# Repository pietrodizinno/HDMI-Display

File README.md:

# HDMI-Display / HDMI to RGB Adapter
Universal HDMI/DVI Displays with Touch Panel based on TI TFP401 and Atmel ATmega32u4 (with Arduino Leonardo compatible Bootloader).

## Shop
* [HDMI to RGB Adapter](http://www.watterott.com/en/HDMI-RGB-adapter-with-ATmega32U4-touch-controller)
* [40-Pin FFC-Extenter](http://www.watterott.com/en/40-Pin-FFC-extenter)
* [Bundle: HDMI Adapter + 5" 800x480 Display with Touchpanel](http://www.watterott.com/en/5-800x480-HDMI-Display-with-resistive-touch)
* [Bundle: HDMI Adapter + 7" 800x480 Display with Touchpanel](http://www.watterott.com/en/7-800x480-HDMI-Display-with-resistive-touch)
* Compatible TFT-Displays *(check jumper settings before connecting the screen)*:
  * [5" 800x480 Display with resitive Touchpanel](http://www.watterott.com/en/5-800x480-TFT-Display)
  * [7" 800x480 Display with resitive Touchpanel](http://www.watterott.com/en/7-800x480-TFT-Display)
  * [7" 800x480 Display with capacitive Touchpanel](http://www.watterott.com/en/7-inch-800x480-TFT-LCD-Display-with-capacitive-touch-panel)
  * [7" 1024x600 Display with capacitive Touchpanel](http://www.watterott.com/en/7-inch-1024x600-TFT-LCD-Display-with-capacitive-touch-panel) *(needs hardware modification on backlight circuit)*

## Features
* TI **TFP401A** HDMI to RGB Converter
* Pixel Rates up to 165MHz, 1080p and WUXGA (1920x1200) at 60Hz
* HDMI compatible (DVI, no Sound, no HDCP, no CEC)
* Atmel **ATmega32U4** Microcontroller to control Backlight and Touch Panel (USB HID Mouse)
* **EDID** EEPROM (24LC02B) for display settings
* LED Backlight Boost Regulator (up to 35V)
* 3.3V - 5V tolerant UART and I2C interface
* **Single 5V Power Supply** via MicroUSB connector

## Hardware and Software
* [Schematics/Layout + Guide](https://github.com/watterott/HDMI-Display/tree/master/pcb)
* [Firmware for ATmega32U4 Microcontroller](https://github.com/watterott/HDMI-Display/tree/master/src)
* [Displays Compatibility List](https://github.com/watterott/HDMI-Display/blob/master/docu/Displays.md)
* [FAQ (Frequently Asked Questions)](https://github.com/watterott/HDMI-Display/blob/master/docu/FAQ.md)
* [Enclosures (3D models)](https://www.thingiverse.com/search?q=watterott+display)

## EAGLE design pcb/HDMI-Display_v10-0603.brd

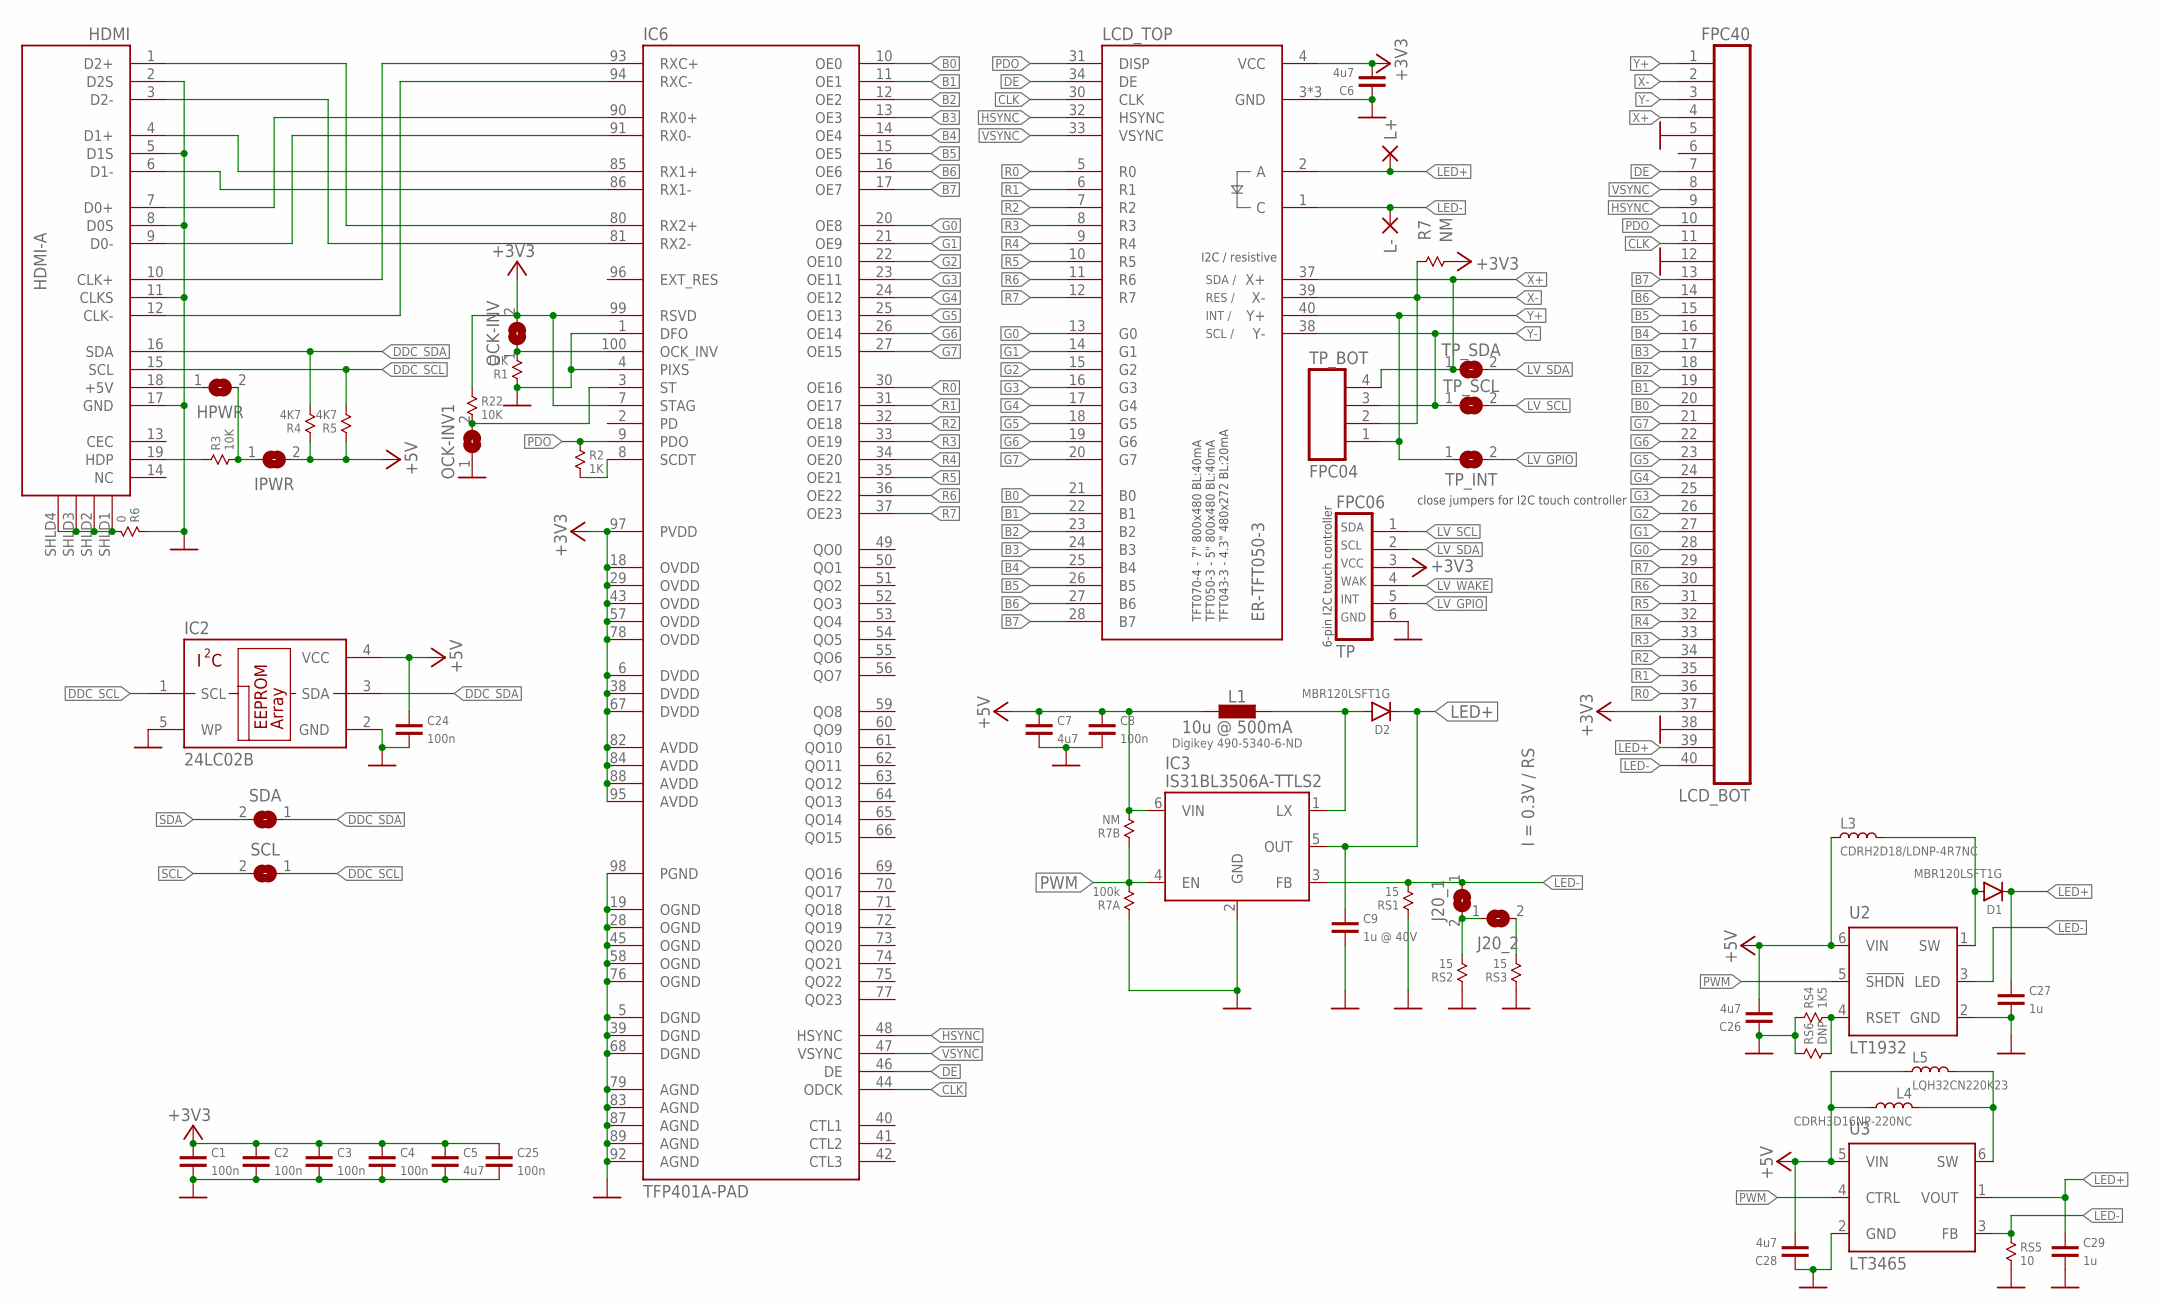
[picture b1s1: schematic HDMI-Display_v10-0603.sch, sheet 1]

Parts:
C1, C2, C3, C4, C8, C24, C25: 100n; 0603
C5, C6, C7, C26, C28: 4u7; 0603
C9: 1u @ 40V; 0805
C27, C29: 1u; 0603
D1, D2: MBR120LSFT1G; SOD-123
HDMI: HDMI-A; HDMI_10029449
HPWR: JUMPER2-0603
IC2: 24LC02B; SOT23-5
IC3: IS31BL3506A-TTLS2; SOT23-6
IC6: TFP401A-PAD; TQFP100-PAD
IPWR: JUMPER2-0603
J20_1, J20_2: JUMPER2-0402
L1: 10u @ 500mA; L_1212
L3: CDRH2D18/LDNP-4R7NC; CDRH2D18
L4: CDRH3D16NP-220NC; CDRH3D16
L5: LQH32CN220K23; LQH32CN_23/LQH32CN_33
L+: PAD-0.80X1.60_NC
L-: PAD-0.80X1.60_NC
LCD_BOT: FPC40
LCD_TOP: ER-TFT050-3; FPC40
OCK-INV, OCK-INV1: JUMPER2-0603-NC; JUMPER2-0603_NC
R1, R3, R22: 10K; 0603
R2: 1K; 0603
R4, R5: 4K7; 0603
R6: 0; 0603
R7, R7B: NM; 0603
R7A: 100k; 0603
RS1, RS2, RS3: 15; 0603
RS4: 1K5; 0603
RS5: 10; 0603
RS6: DNP; 0603
SCL: JUMPER2-0603
SDA: JUMPER2-0603
TP: FPC06
TP_BOT: FPC04
TP_INT: JUMPER2-0402
TP_SCL: JUMPER2-0402
TP_SDA: JUMPER2-0402
U2: LT1932; SOT23-6
U3: LT3465; SOT23-6

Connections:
+3V3: C1.2, C2.2, C3.2, C4.2, C5.2, C6.1, C25.2, IC6.6 (DVDD), IC6.7 (STAG), IC6.18 (OVDD), IC6.29 (OVDD), IC6.38 (DVDD), IC6.43 (OVDD), IC6.57 (OVDD), IC6.67 (DVDD), IC6.78 (OVDD), IC6.82 (AVDD), IC6.84 (AVDD), IC6.88 (AVDD), IC6.95 (AVDD), IC6.97 (PVDD), IC6.99 (RSVD), LCD_BOT.37, LCD_TOP.4 (VCC), OCK-INV.2, R7.2, R22.1, TP.3; also elsewhere on the board
+5V: C7.2, C8.2, C24.2, C26.1, C28.1, IC2.4 (VCC), IC3.6 (VIN), IPWR.2, L1.1, L3.1, L4.2, L5.1, R4.1, R5.1, R7B.2, U2.6 (VIN), U3.5 (VIN); also elsewhere on the board
B0: IC6.10 (OE0), LCD_BOT.20, LCD_TOP.21 (B0)
B1: IC6.11 (OE1), LCD_BOT.19, LCD_TOP.22 (B1)
B2: IC6.12 (OE2), LCD_BOT.18, LCD_TOP.23 (B2)
B3: IC6.13 (OE3), LCD_BOT.17, LCD_TOP.24 (B3)
B4: IC6.14 (OE4), LCD_BOT.16, LCD_TOP.25 (B4)
B5: IC6.15 (OE5), LCD_BOT.15, LCD_TOP.26 (B5)
B6: IC6.16 (OE6), LCD_BOT.14, LCD_TOP.27 (B6)
B7: IC6.17 (OE7), LCD_BOT.13, LCD_TOP.28 (B7)
CLK: IC6.44 (ODCK), LCD_BOT.11, LCD_TOP.30 (CLK)
CLK_N: HDMI.12 (CLK-), IC6.94 (RXC-)
CLK_P: HDMI.10 (CLK+), IC6.93 (RXC+)
D0_N: HDMI.9 (D0-), IC6.91 (RX0-)
D0_P: HDMI.7 (D0+), IC6.90 (RX0+)
D1_N: HDMI.6 (D1-), IC6.86 (RX1-)
D1_P: HDMI.4 (D1+), IC6.85 (RX1+)
D2_N: HDMI.3 (D2-), IC6.81 (RX2-)
D2_P: HDMI.1 (D2+), IC6.80 (RX2+)
DDC_SCL: HDMI.15 (SCL), IC2.1 (SCL), R5.2, SCL.1
DDC_SDA: HDMI.16 (SDA), IC2.3 (SDA), R4.2, SDA.1
DE: IC6.46 (DE), LCD_BOT.7, LCD_TOP.34 (DE)
G0: IC6.20 (OE8), LCD_BOT.28, LCD_TOP.13 (G0)
G1: IC6.21 (OE9), LCD_BOT.27, LCD_TOP.14 (G1)
G2: IC6.22 (OE10), LCD_BOT.26, LCD_TOP.15 (G2)
G3: IC6.23 (OE11), LCD_BOT.25, LCD_TOP.16 (G3)
G4: IC6.24 (OE12), LCD_BOT.24, LCD_TOP.17 (G4)
G5: IC6.25 (OE13), LCD_BOT.23, LCD_TOP.18 (G5)
G6: IC6.26 (OE14), LCD_BOT.22, LCD_TOP.19 (G6)
G7: IC6.27 (OE15), LCD_BOT.21, LCD_TOP.20 (G7)
GND: C1.1, C2.1, C3.1, C4.1, C5.1, C6.2, C7.1, C8.1, C9.1, C24.1, C25.1, C26.2, C27.1, C28.2, C29.1, HDMI.2 (D2S), HDMI.5 (D1S), HDMI.8 (D0S), HDMI.11 (CLKS), HDMI.17 (GND), IC2.2 (GND), IC2.5 (WP), IC3.2 (GND), IC6.1 (DFO), IC6.4 (PIXS), IC6.5 (DGND), IC6.19 (OGND), IC6.28 (OGND), IC6.39 (DGND), IC6.45 (OGND), IC6.58 (OGND), IC6.68 (DGND), IC6.76 (OGND), IC6.79 (AGND), IC6.83 (AGND), IC6.87 (AGND), IC6.89 (AGND), IC6.92 (AGND), IC6.98 (PGND), LCD_BOT.5, LCD_BOT.12, LCD_BOT.38, LCD_TOP.3 (GND), LCD_TOP.29 (GND), LCD_TOP.36 (GND), OCK-INV1.1, R1.1, R6.1, R7A.1, RS1.1, RS2.1, RS3.1, RS4.1, RS5.2, RS6.1, TP.6, U2.2 (GND), U3.2 (GND); also elsewhere on the board
HDMI_5V: HDMI.18 (+5V), HPWR.1
HDMI_DECT: HDMI.19 (HDP), R3.1
HSYNC: IC6.48 (HSYNC), LCD_BOT.9, LCD_TOP.32 (HSYNC)
LED+: C9.2, C27.2, C29.2, D1.C, D2.C, IC3.5 (OUT), L+.1, LCD_BOT.39, LCD_TOP.2 (A), U3.1 (VOUT)
LED-: IC3.3 (FB), J20_1.1, L-.1, LCD_BOT.40, LCD_TOP.1 (C), RS1.2, RS5.1, U2.3 (LED), U3.3 (FB)
LV_GPIO: TP.5, TP_INT.2; also elsewhere on the board
LV_SCL: TP.1, TP_SCL.2; also elsewhere on the board
LV_SDA: TP.2, TP_SDA.2; also elsewhere on the board
LV_WAKE: TP.4
LX: D2.A, IC3.1 (LX), L1.2
unnamed: J20_2.2, RS3.2
unnamed: J20_1.2, J20_2.1, RS2.2
unnamed: IC6.100 (OCK_INV), OCK-INV.1, R1.2
unnamed: IC6.3 (ST), OCK-INV1.2, R22.2
unnamed: HPWR.2, IPWR.1, R3.2
unnamed: RS4.2, RS6.2, U2.4 (RSET)
unnamed: D1.A, L3.2, U2.1 (SW)
unnamed: L4.1, L5.2, U3.6 (SW)
PDO: IC6.9 (PDO), LCD_BOT.10, LCD_TOP.31 (DISP), R2.1
PWM: IC3.4 (EN), R7A.2, R7B.1, U2.5 (!SHDN), U3.4 (CTRL); also elsewhere on the board
R0: IC6.30 (OE16), LCD_BOT.36, LCD_TOP.5 (R0)
R1: IC6.31 (OE17), LCD_BOT.35, LCD_TOP.6 (R1)
R2: IC6.32 (OE18), LCD_BOT.34, LCD_TOP.7 (R2)
R3: IC6.33 (OE19), LCD_BOT.33, LCD_TOP.8 (R3)
R4: IC6.34 (OE20), LCD_BOT.32, LCD_TOP.9 (R4)
R5: IC6.35 (OE21), LCD_BOT.31, LCD_TOP.10 (R5)
R6: IC6.36 (OE22), LCD_BOT.30, LCD_TOP.11 (R6)
R7: IC6.37 (OE23), LCD_BOT.29, LCD_TOP.12 (R7)
SCDT: IC6.8 (SCDT), R2.2
SCL: SCL.2; also elsewhere on the board
SDA: SDA.2; also elsewhere on the board
SHLD3: HDMI.SHLD1 (SHLD), HDMI.SHLD2 (SHLD), HDMI.SHLD3 (SHLD), HDMI.SHLD4 (SHLD), R6.2
VSYNC: IC6.47 (VSYNC), LCD_BOT.8, LCD_TOP.33 (VSYNC)
X+: LCD_BOT.4, LCD_TOP.37 (X+), TP_BOT.4, TP_SDA.1; also elsewhere on the board
X-: LCD_BOT.2, LCD_TOP.39 (X-), R7.1, TP_BOT.2; also elsewhere on the board
Y+: LCD_BOT.1, LCD_TOP.40 (Y+), TP_BOT.1, TP_INT.1; also elsewhere on the board
Y-: LCD_BOT.3, LCD_TOP.38 (Y-), TP_BOT.3, TP_SCL.1; also elsewhere on the board

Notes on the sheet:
I = 0.3V / RS
Digikey 490-5340-6-ND
TFT070-4 - 7" 800x480 BL:40mA TFT050-3 - 5" 800x480 BL:40mA TFT043-3 - 4.3" 480x272 BL:20mA
SDA /
SCL /
RES /
INT /
SDA
SCL
VCC
INT
WAK
GND
close jumpers for I2C touch controller
6-pin I2C touch controller
I2C / resistive

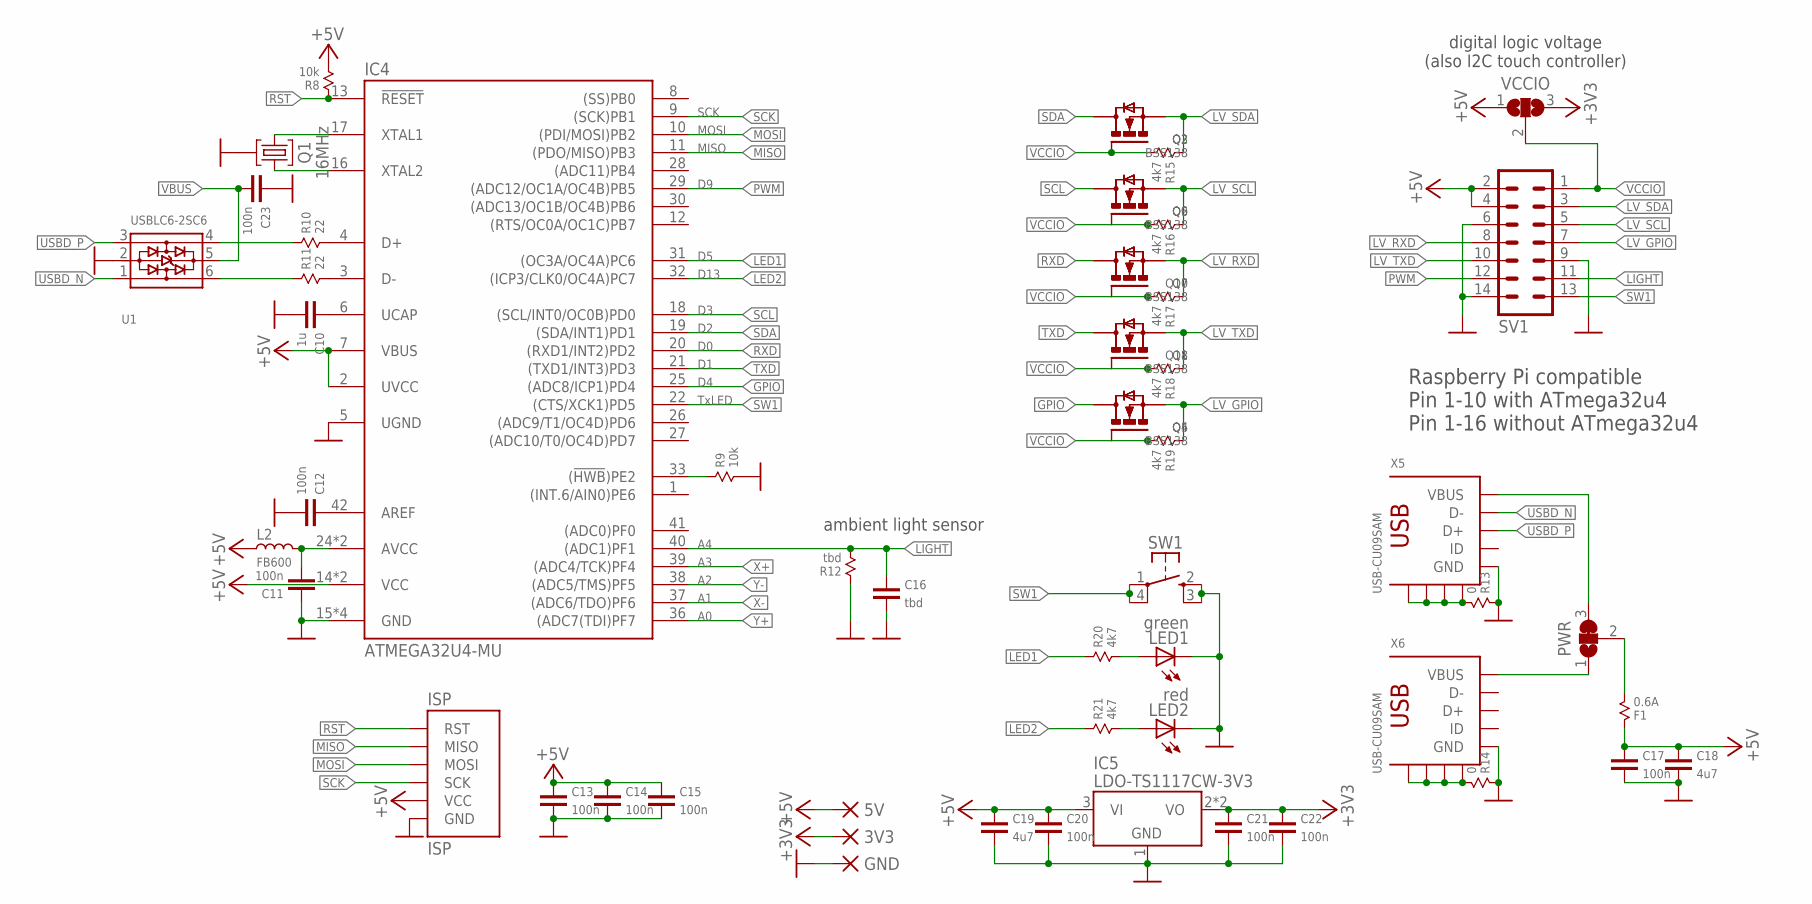
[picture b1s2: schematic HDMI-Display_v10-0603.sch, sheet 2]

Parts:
3V3, 5V: PAD-1.27X1.27_NC
C10: 1u; 0603
C11, C12, C13, C14, C15, C17, C20, C21, C22, C23: 100n; 0603
C16: tbd; 0603
C18, C19: 4u7; 0603
F1: 0.6A; 0805
GND: PAD-1.27X1.27_NC
IC4: ATMEGA32U4-MU; QFN44
IC5: LDO-TS1117CW-3V3; SOT223
ISP: ISP
L2: FB600; 0603
LED1: green; LED_0603
LED2: red; LED_0603
PWR: JUMPER3-0603
Q1: 16MHz; CRYSTAL_32X13
Q2, Q5, Q6, Q7, Q8: MOSFET-N-SOT323; SOT323
Q3, Q4, Q9, Q10, Q11: BSS138; SOT-23
R8, R9: 10k; 0603
R10, R11: 22; 0603
R12: tbd; 0603
R13, R14: 0; 0603
R15, R16, R17, R18, R19, R20, R21: 4k7; 0603
SV1: MA07-2
SW1: SW-TACTILE-TL3315; SW_TL3315N
U1: USBLC6-2SC6; SOT23-6
VCCIO: JUMPER3-0603-NC; JUMPER3-0603_NC
X5, X6: USB-CU09SAM; CU09SAM

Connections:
+3V3: 3V3.1, C21.2, C22.2, IC5.2 (VO), IC5.4 (VO), VCCIO.3; also elsewhere on the board
+5V: 5V.1, C13.2, C14.2, C15.2, C17.2, C18.2, C19.2, C20.2, F1.1, IC4.2 (UVCC), IC4.7 (VBUS), IC4.14 (VCC), IC4.34 (VCC), IC5.3 (VI), ISP.VCC, L2.1, R8.2, SV1.2, SV1.4, VCCIO.1; also elsewhere on the board
AREF: C12.2, IC4.42 (AREF)
AVCC: C11.1, IC4.24 (AVCC), IC4.44 (AVCC), L2.2
D_N: IC4.3 (D-), R11.2
D_P: IC4.4 (D+), R10.2
GND: C10.1, C11.2, C12.1, C13.1, C14.1, C15.1, C16.1, C17.1, C18.1, C19.1, C20.1, C21.1, C22.1, C23.2, GND.1, IC4.5 (UGND), IC4.15 (GND), IC4.23 (GND), IC4.35 (GND), IC4.43 (GND), IC5.1 (GND), ISP.GND, LED1.C, LED2.C, Q1.GND, R9.2, R12.1, R13.1, R14.1, SV1.6, SV1.9, SV1.14, SW1.2 (S1), SW1.3 (S2), U1.2 (GND), X5.5 (GND), X6.5 (GND); also elsewhere on the board
GPIO: IC4.25 ((ADC8/ICP1)PD4), Q4.3 (D), Q5.3 (D)
HWB: IC4.33 ((!HWB!)PE2), R9.1
LED1: IC4.31 ((OC3A/OC4A)PC6), R20.1
LED2: IC4.32 ((ICP3/CLK0/OC4A)PC7), R21.1
LIGHT: C16.2, IC4.40 ((ADC1)PF1), R12.2, SV1.11
LV_GPIO: Q4.2 (S), Q5.2 (S), R19.1, SV1.7; also elsewhere on the board
LV_RXD: Q7.2 (S), Q10.2 (S), R17.1, SV1.8
LV_SCL: Q6.2 (S), Q9.2 (S), R16.1, SV1.5; also elsewhere on the board
LV_SDA: Q2.2 (S), Q3.2 (S), R15.1, SV1.3; also elsewhere on the board
LV_TXD: Q8.2 (S), Q11.2 (S), R18.1, SV1.10
MISO: IC4.11 ((PDO/MISO)PB3), ISP.MISO
MOSI: IC4.10 ((PDI/MOSI)PB2), ISP.MOSI
unnamed: R11.1, U1.6 (IO1)
unnamed: R10.1, U1.4 (IO2)
unnamed: C10.2, IC4.6 (UCAP)
unnamed: F1.2, PWR.2
unnamed: LED1.A, R20.2
unnamed: LED2.A, R21.2
PWM: IC4.29 ((ADC12/OC1A/OC4B)PB5), SV1.12; also elsewhere on the board
RST: IC4.13 (!RESET), ISP.RST, R8.1
RXD: IC4.20 ((RXD1/INT2)PD2), Q7.3 (D), Q10.3 (D)
SCK: IC4.9 ((SCK)PB1), ISP.SCK
SCL: IC4.18 ((SCL/INT0/OC0B)PD0), Q6.3 (D), Q9.3 (D); also elsewhere on the board
SDA: IC4.19 ((SDA/INT1)PD1), Q2.3 (D), Q3.3 (D); also elsewhere on the board
SHLD1: R13.2, X5.GND@1 (GND), X5.GND@2 (GND), X5.GND@3 (GND), X5.GND@4 (GND)
SHLD2: R14.2, X6.GND@1 (GND), X6.GND@2 (GND), X6.GND@3 (GND), X6.GND@4 (GND)
SW1: IC4.22 ((CTS/XCK1)PD5), SV1.13, SW1.1, SW1.4 (P2)
TXD: IC4.21 ((TXD1/INT3)PD3), Q8.3 (D), Q11.3 (D)
USBD_N: U1.1 (IO1), X5.2 (D-)
USBD_P: U1.3 (IO2), X5.3 (D+)
VBUS: C23.1, PWR.3, U1.5 (VBUS), X5.1 (VBUS)
VBUS_PWR: PWR.1, X6.1 (VBUS)
VCCIO: Q2.1 (G), Q3.1 (G), Q4.1 (G), Q5.1 (G), Q6.1 (G), Q7.1 (G), Q8.1 (G), Q9.1 (G), Q10.1 (G), Q11.1 (G), R15.2, R16.2, R17.2, R18.2, R19.2, SV1.1, VCCIO.2
X+: IC4.39 ((ADC4/TCK)PF4); also elsewhere on the board
X-: IC4.37 ((ADC6/TDO)PF6); also elsewhere on the board
XTAL1: IC4.17 (XTAL1), Q1.2
XTAL2: IC4.16 (XTAL2), Q1.1
Y+: IC4.36 ((ADC7(TDI)PF7); also elsewhere on the board
Y-: IC4.38 ((ADC5/TMS)PF5); also elsewhere on the board

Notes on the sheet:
ambient light sensor
TxLED
D13
SCK
MOSI
MISO
Raspberry Pi compatible Pin 1-10 with ATmega32u4 Pin 1-16 without ATmega32u4
digital logic voltage (also I2C touch controller)

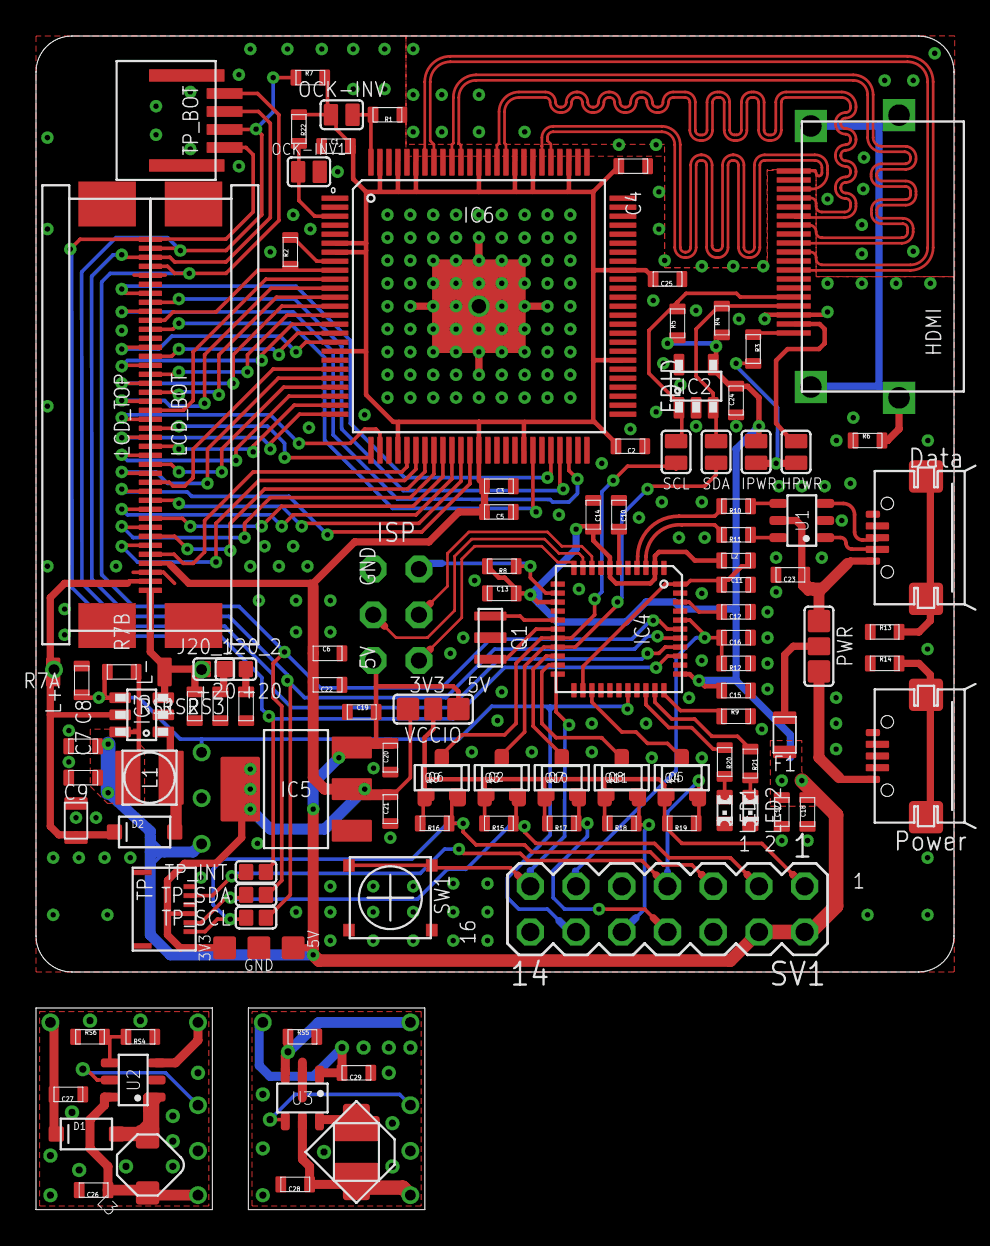
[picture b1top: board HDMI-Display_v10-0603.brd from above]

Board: 2 copper layers, 51.0 x 52.0 mm, 116 parts (0 on the bottom side), 100 nets.

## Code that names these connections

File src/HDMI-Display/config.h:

#ifndef CONFIG_H
#define CONFIG_H

//***** Select your Display and Touchpanel here ******
#define DISPLAY_TYPE            DISPLAY_480x272 // DISPLAY_480x272 DISPLAY_800x480 DISPLAY_800x480HY DISPLAY_1024x600HY
#define TOUCHPANEL_TYPE         TOUCHPANEL_NONE // TOUCHPANEL_NONE TOUCHPANEL_RESISTIVE TOUCHPANEL_FT5x06

/*
  Watterott electronic display configurations:
  5" with res. touch: DISPLAY_800x480 + TOUCHPANEL_RESISTIVE
  7" with res. touch: DISPLAY_800x480 + TOUCHPANEL_RESISTIVE
  7" with cap. touch: DISPLAY_800x480HY or DISPLAY_1024x600HY + TOUCHPANEL_FT5x06
*/

// General Settings
//#define DEBUG             1 // set debugg output level (0=nothing, 1=minimal...)
#define ORIENTATION       0 // orientation (0x1=invert x, 0x2=invert y, 0x4=swap axes, 0x8=map to screen coordinates)
#define SCREENSAVERTIME 180 // seconds timeout (0...65535, 0=always on)
#define BRIGHTNESS      255 // backlight brightness (0..255)
#define LOOPTIME         16 // 16 = 60 Hz polling interval
#define TOUCHMAX      4095L // maximal touch/mouse position

#define QUOTE(name)     #name
#define STR(macro)      QUOTE(macro)
#define VERSION_STRING  "1.10"
#define INFO_STRING     "HDMI-Display\nVersion: " VERSION_STRING " (" __DATE__ ")\nTFT: " STR(SCREEN_WIDTH) "x" STR(SCREEN_HEIGHT)"\nTouch: " STR(TOUCHPANEL_TYPE) "\nhttps://github.com/watterott/HDMI-Display"

// Display Types
#define DISPLAY_480x272          1 //  480 x  272 (TFT043-3)
#define DISPLAY_640x480          2 //  640 x  480
#define DISPLAY_720x480          3 //  720 x  480
#define DISPLAY_800x480          4 //  800 x  480 (TFT050-3, HY5-LCD-HD, TFT070-4, HY7-LCD)
#define DISPLAY_800x480_720x480  5 //  800 x  480 with 720x480 (480p) fallback (TFT050-3, HY5-LCD-HD, TFT070-4, HY7-LCD)
#define DISPLAY_800x480HY        6 //  800 x  480 (HY070CTP capacitive touchpanel)
#define DISPLAY_800x600          7 //  800 x  600
#define DISPLAY_1024x600         8 // 1024 x  600
#define DISPLAY_1024x600HY       9 // 1024 x  600 (HY070CTP-HD capacitive touchpanel)
#define DISPLAY_1024x768        10 // 1024 x  768
#define DISPLAY_1280x720        11 // 1280 x  720
#define DISPLAY_1280x768        12 // 1280 x  768
#define DISPLAY_1280x800        13 // 1280 x  800
#define DISPLAY_1280x1024       14 // 1280 x 1024

// Touchpanel Types
#define TOUCHPANEL_NONE         1 // No Touchpanel present
#define TOUCHPANEL_RESISTIVE    2 // Resitive
#define TOUCHPANEL_FT5x06       3 // Capacitive FT5x06 (HY070CTP)

// check configurations
#if TOUCHPANEL_TYPE == TOUCHPANEL_NONE
#  undef SCREENSAVERTIME
#  define SCREENSAVERTIME 0
#  define TPC_X0 0    // not needed - touchpanel calibration x0
#  define TPC_X1 0    // not needed - touchpanel calibration x1
#  define TPC_Y0 0    // not needed - touchpanel calibration y0
#  define TPC_Y1 0    // not needed - touchpanel calibration y1
#elif TOUCHPANEL_TYPE == TOUCHPANEL_RESISTIVE
#  define TPC_X0 80   // touchpanel calibration x0
#  define TPC_X1 930  // touchpanel calibration x1
#  define TPC_Y0 825  // touchpanel calibration y0
#  define TPC_Y1 160  // touchpanel calibration y1
#elif TOUCHPANEL_TYPE == TOUCHPANEL_FT5x06
#  define TPC_X0 0    // not needed - touchpanel calibration x0
#  define TPC_X1 0    // not needed - touchpanel calibration x1
#  define TPC_Y0 0    // not needed - touchpanel calibration y0
#  define TPC_Y1 0    // not needed - touchpanel calibration y1
#else
#  error "Please select a TOUCHPANEL_TYPE"
#endif

#if DISPLAY_TYPE == DISPLAY_480x272
#  define SCREEN_WIDTH   480
#  define SCREEN_HEIGHT  272
#elif DISPLAY_TYPE == DISPLAY_640x480
#  define SCREEN_WIDTH   640
#  define SCREEN_HEIGHT  480
#elif DISPLAY_TYPE == DISPLAY_720x480
#  define SCREEN_WIDTH   720
#  define SCREEN_HEIGHT  480
#elif DISPLAY_TYPE == DISPLAY_800x480 || \
      DISPLAY_TYPE == DISPLAY_800x480_720x480 || \
      DISPLAY_TYPE == DISPLAY_800x480HY
#  define SCREEN_WIDTH   800
#  define SCREEN_HEIGHT  480
#elif DISPLAY_TYPE == DISPLAY_800x600
#  define SCREEN_WIDTH   800
#  define SCREEN_HEIGHT  600
#elif DISPLAY_TYPE == DISPLAY_1024x600 || \
      DISPLAY_TYPE == DISPLAY_1024x600HY
#  define SCREEN_WIDTH   1024
#  define SCREEN_HEIGHT  600
#elif DISPLAY_TYPE == DISPLAY_1024x768
#  define SCREEN_WIDTH   1024
#  define SCREEN_HEIGHT  768
#elif DISPLAY_TYPE == DISPLAY_1280x720
#  define SCREEN_WIDTH   1280
#  define SCREEN_HEIGHT  720
#elif DISPLAY_TYPE == DISPLAY_1280x768
#  define SCREEN_WIDTH   1280
#  define SCREEN_HEIGHT  768
#elif DISPLAY_TYPE == DISPLAY_1280x800
#  define SCREEN_WIDTH   1280
#  define SCREEN_HEIGHT  800
#elif DISPLAY_TYPE == DISPLAY_1280x1024
#  define SCREEN_WIDTH   1280
#  define SCREEN_HEIGHT  1024
#else
#  error "Please select a DISPLAY_TYPE"
#endif

#ifndef SWAP
#define SWAP(x,y) do{ (x)=(x)^(y); (y)=(x)^(y); (x)=(x)^(y); }while(0)
#endif

// IO ports
#define LED_1           5 // first LED PC6
#define LED_2          13 // second LED PC7
#define BACKLIGHT       9 // backlight control PB5
#define SW_1       (1<<5) // switch PD5
#define INT             4 // touch interrupt PD4
#define SW_1_SETUP() PORTD |= SW_1; DDRD &= ~SW_1 // set input
#define SW_1_PRESSED() (!(PIND & SW_1)) // switch pressed?

// Touchpanel analog inputs 
#define AXM            A1 // touch X- PF6
#define AXP            A3 // touch X+ PF4
#define AYM            A2 // touch Y- PF5
#define AYP            A0 // touch Y+ PF7

// External EDID EEPROM
#define EEPROMSIZE 128  // size in bytes
#define EEPROMADDR 0x50 // I2C address

#endif //CONFIG_H

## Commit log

2015-07-23 Add version with 0603 components. Add backlight controllers on LT1932 and LT3465.
2015-07-23 Change README.md
2015-07-23 Change pcb image
2015-07-23 Change Readme
2016-01-11 Initial changes
